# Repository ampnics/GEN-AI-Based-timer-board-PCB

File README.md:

Gen-AI-Based Timer Board using KiCad and DeepSeek
This project demonstrates the design of a timer control board created using traditional EDA tools supported by generative AI guidance. The goal was to explore how AI can assist in real-world hardware development, from concept to PCB.

Overview
This timer board is designed for applications such as:

Delay-based relay switching

Countdown-based automation

General purpose timing control in embedded systems

It features an ESP-based controller, a relay driver circuit, an OLED display for user feedback, and input buttons for setting time values.

AI Collaboration using DeepSeek
Throughout the project, DeepSeek AI was used to accelerate and refine different stages of the hardware design process:

Block Diagram: AI-generated block-level architecture based on system description.

Schematic Design: Assisted in part selection, logic validation, and drawing guidance.

Design Review: Suggested improvements for schematic correctness and layout optimization.

PCB Layout: Provided tips for routing, placement, EMI handling, and power distribution.

Design Feedback: Rated final design and recommended minor refinements.

Tools Used
KiCad 7.x for schematic and PCB design

DeepSeek AI for design assistance and review

ESP-based microcontroller

Relay module and driver circuitry

OLED I2C display

Tactile push buttons

Repository Structure
/kicad_project: Contains KiCad schematic and PCB layout files

/gerbers: Fabrication-ready Gerber files

/images: Block diagram, schematic snapshots, and board render

/docs: Design notes, AI feedback logs, and changelog

How to Use
Clone the repository

Open the KiCad project from the kicad_project folder

Review or modify the schematic as needed

Generate or inspect Gerber files for fabrication

Refer to the /docs folder for design rationale and review feedback

License
This project is open-sourced under the MIT License. You are free to use, modify, and distribute it for personal or commercial use.

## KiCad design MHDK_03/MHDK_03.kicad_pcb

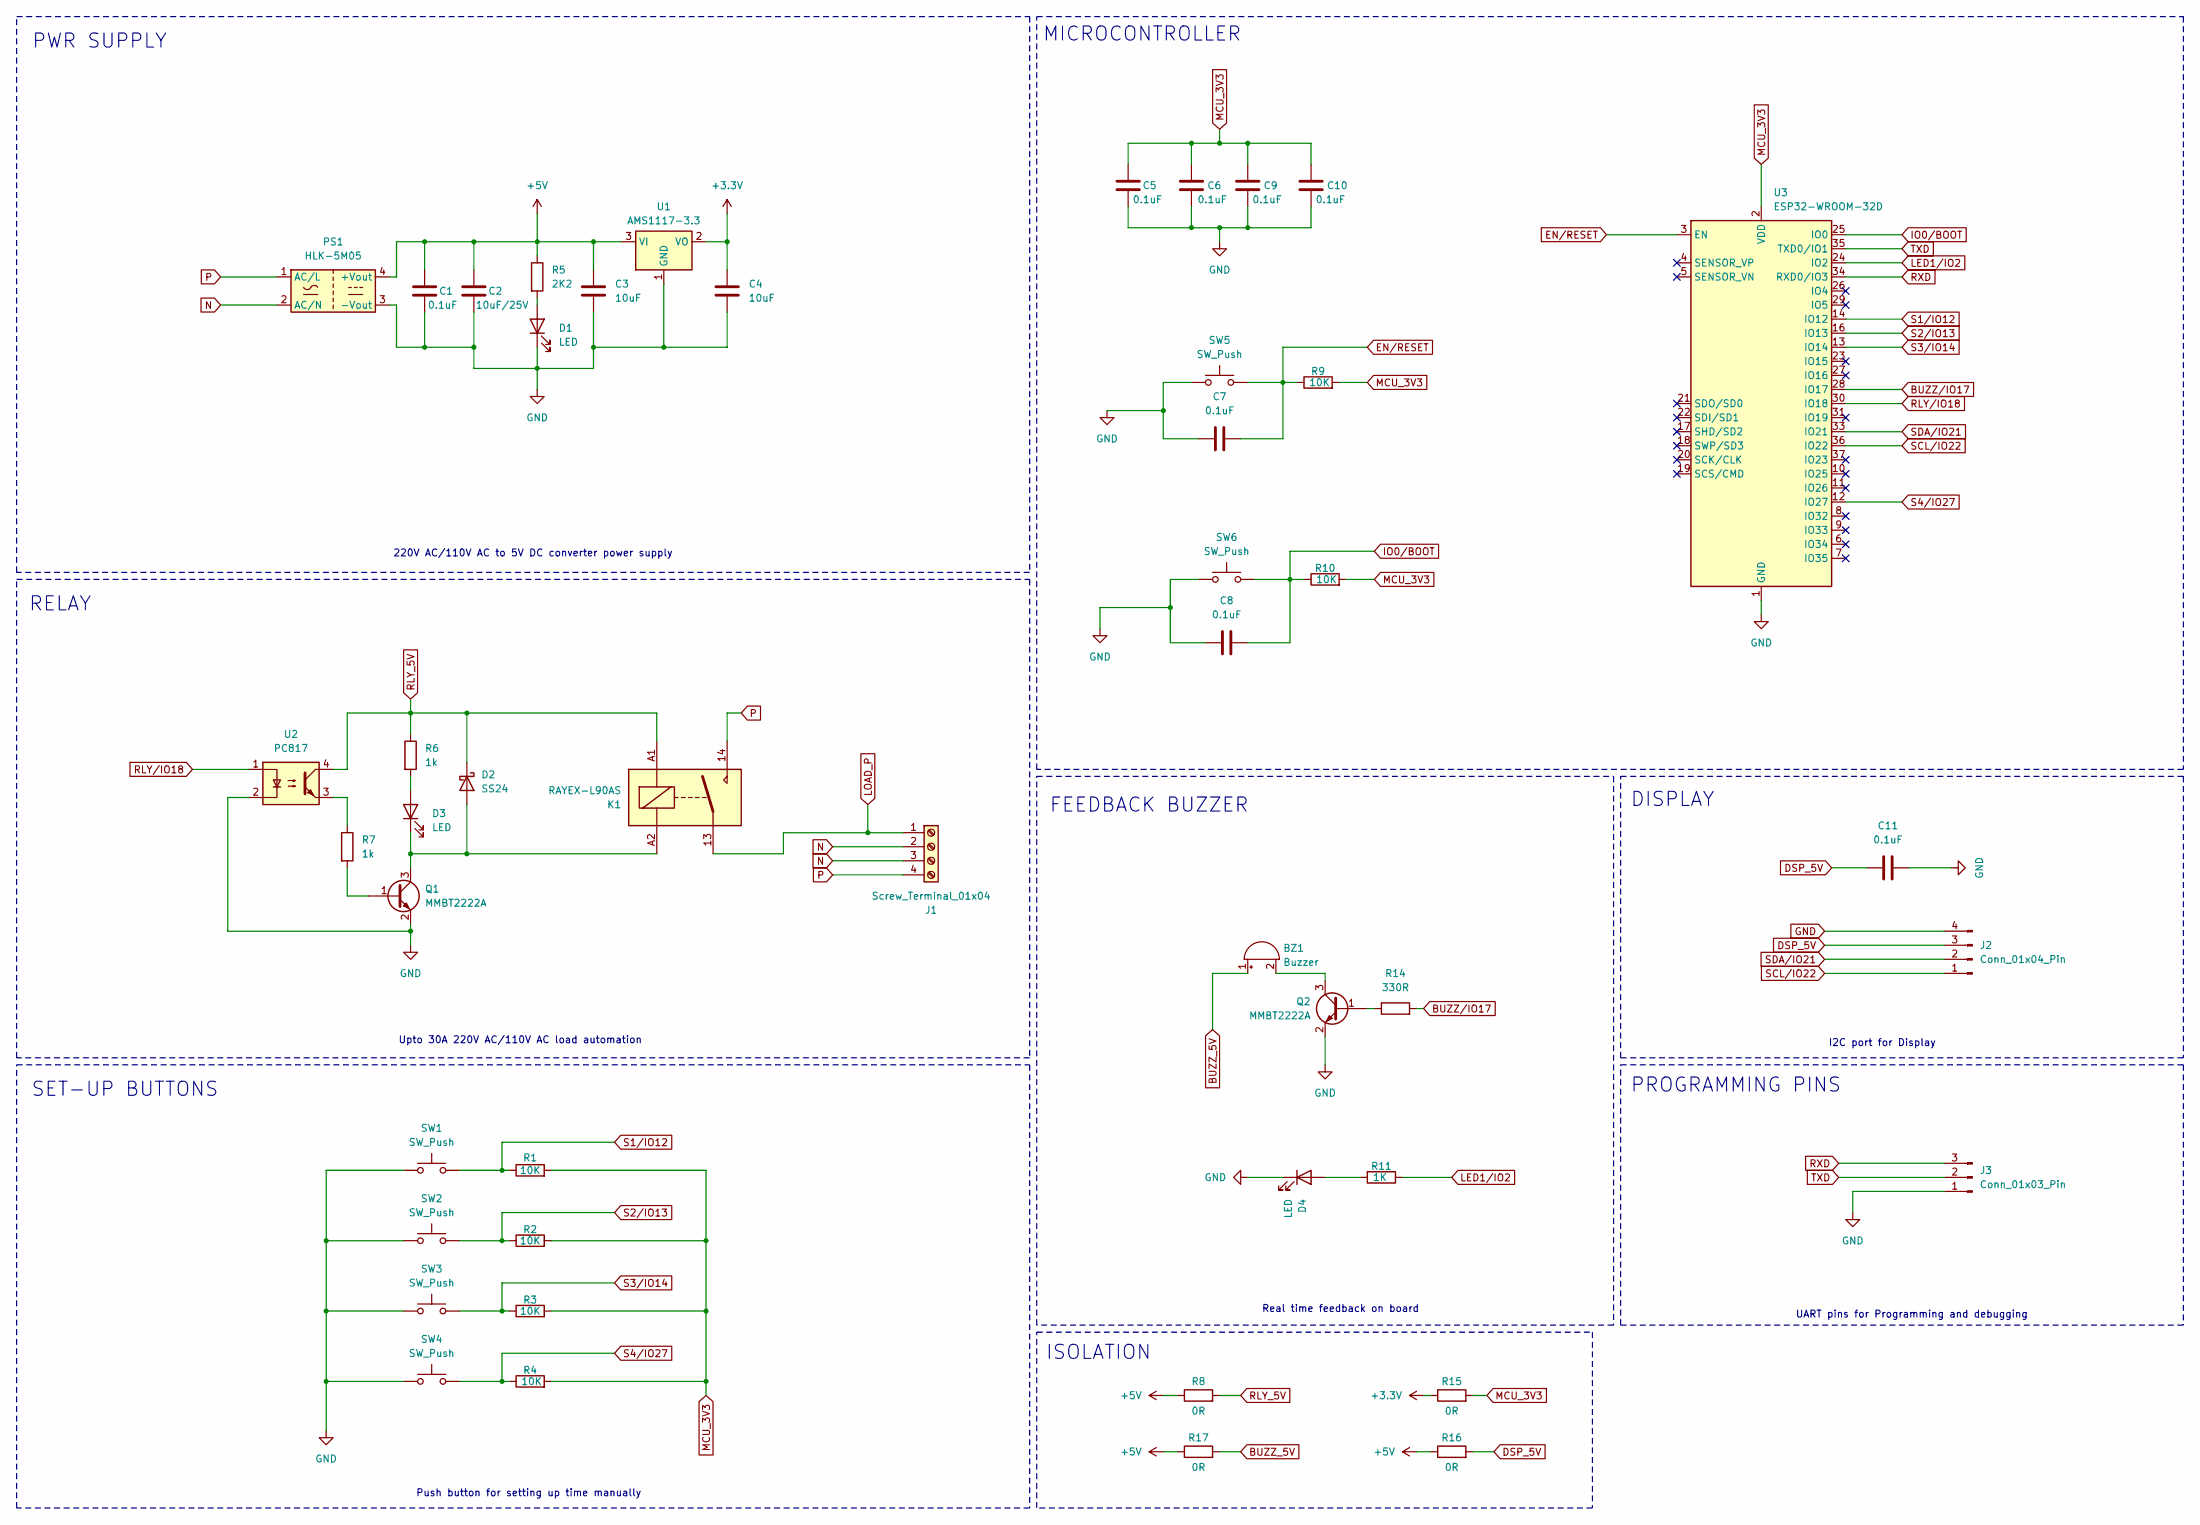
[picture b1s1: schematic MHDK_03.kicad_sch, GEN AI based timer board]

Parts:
BZ1: Buzzer; Buzzer_12x9.5RM7.6
C1, C5, C6, C7, C8, C9, C10, C11: 0.1uF; C_0805_2012Metric
C2: 10uF/25V; C_1206_3216Metric
C3, C4: 10uF; C_1206_3216Metric
D1, D3, D4: LED; LED_0805_2012Metric
D2: SS24; D_SMA
J1: Screw_Terminal_01x04; TerminalBlock_bornier-4_P5.08mm
J2: Conn_01x04_Pin; JST_XH_B4B-XH-A_1x04_P2.50mm_Vertical
J3: Conn_01x03_Pin; PinSocket_1x03_P2.54mm_Vertical
K1: RAYEX-L90AS; Relay_SPST_RAYEX-L90AS
PS1: HLK-5M05; Converter_ACDC_Hi-Link_HLK-5Mxx
Q1, Q2: MMBT2222A; SOT-23
R1, R2, R3, R4, R9, R10: 10K; R_0805_2012Metric
R5: 2K2; R_0805_2012Metric
R6, R7: 1k; R_0805_2012Metric
R8: 0R; R_0805_2012Metric
R11: 1K; R_0805_2012Metric
R14: 330R; R_0805_2012Metric
R15, R16, R17: 0R; R_0603_1608Metric
SW1, SW2, SW3, SW4, SW5: SW_Push; SW_PUSH_6mm
SW6: SW_Push; SW_Push_SPST_NO_Alps_SKRK
U1: AMS1117-3.3; SOT-223-3_TabPin2
U2: PC817; DIP-4_W7.62mm
U3: ESP32-WROOM-32D

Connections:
+3.3V: C4.1, R15.1, U1.2 (VO)
+5V: C1.1, C2.1, C3.1, PS1.4 (+Vout), R5.1, R8.1, R16.1, R17.1, U1.3 (VI)
BUZZ_5V: BZ1.1 (+), R17.2
BUZZ/IO17: R14.2, U3.28 (IO17)
DSP_5V: C11.2, J2.3, R16.2
EN/RESET: C7.2, R9.1, SW5.2, U3.3 (EN)
GND: C1.2, C2.2, C3.2, C4.2, C5.2, C6.2, C7.1, C8.1, C9.2, C10.2, C11.1, D1.1 (K), D4.1 (K), J2.4, J3.1, PS1.3 (-Vout), Q1.2 (E), Q2.2 (E), SW1.1, SW2.1, SW3.1, SW4.1, SW5.1, SW6.1, U1.1 (GND), U2.2, U3.1 (GND), U3.15 (GND), U3.38 (GND), U3.39 (GND)
IO0/BOOT: C8.2, R10.1, SW6.2, U3.25 (IO0)
LED1/IO2: R11.1, U3.24 (IO2)
LOAD_P: J1.1, K1.13
MCU_3V3: C5.1, C6.1, C9.1, C10.1, R1.2, R2.2, R3.2, R4.2, R9.2, R10.2, R15.2, U3.2 (VDD)
N: J1.2, J1.3, PS1.2 (AC/N)
unnamed: BZ1.2 (-), Q2.3 (C)
unnamed: D1.2 (A), R5.2
unnamed: D2.2 (A), D3.1 (K), K1.A2, Q1.3 (C)
unnamed: D3.2 (A), R6.2
unnamed: D4.2 (A), R11.2
unnamed: Q1.1 (B), R7.2
unnamed: Q2.1 (B), R14.1
unnamed: R7.1, U2.3
P: J1.4, K1.14, PS1.1 (AC/L)
RLY_5V: D2.1 (K), K1.A1, R6.1, R8.2, U2.4
RLY/IO18: U2.1, U3.30 (IO18)
RXD: J3.3, U3.34 (RXD0/IO3)
S1/IO12: R1.1, SW1.2, U3.14 (IO12)
S2/IO13: R2.1, SW2.2, U3.16 (IO13)
S3/IO14: R3.1, SW3.2, U3.13 (IO14)
S4/IO27: R4.1, SW4.2, U3.12 (IO27)
SCL/IO22: J2.1, U3.36 (IO22)
SDA/IO21: J2.2, U3.33 (IO21)
TXD: J3.2, U3.35 (TXD0/IO1)

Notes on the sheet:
Push button for setting up time manually
Real time feedback on board
RELAY
SET-UP BUTTONS
Upto 30A 220V AC/110V AC load automation
PROGRAMMING PINS
I2C port for Display
MICROCONTROLLER
PWR SUPPLY
ISOLATION
DISPLAY
220V AC/110V AC to 5V DC converter power supply
UART pins for Programming and debugging
FEEDBACK BUZZER

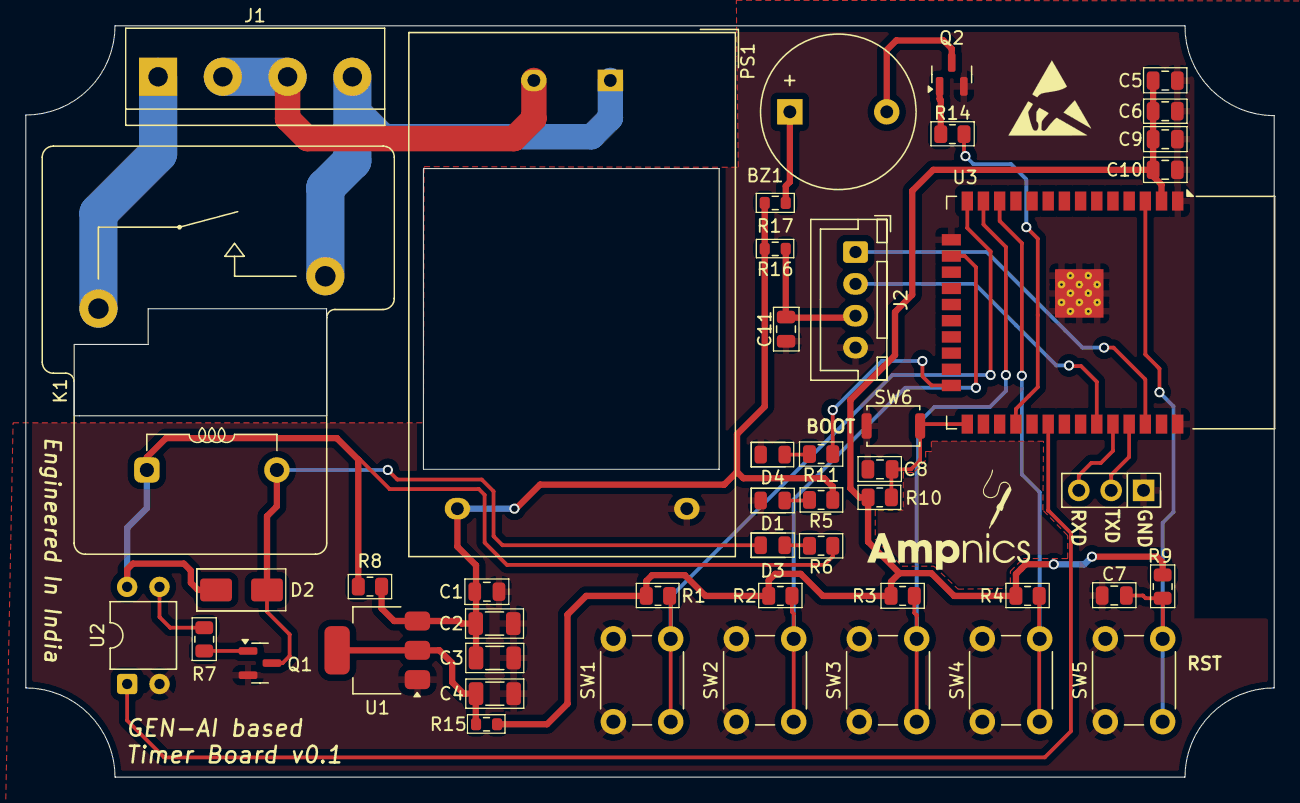
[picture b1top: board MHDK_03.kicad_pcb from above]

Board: 2 copper layers, 97.9 x 58.9 mm, 47 parts (0 on the bottom side), 31 nets.

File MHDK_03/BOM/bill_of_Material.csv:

"Reference","Qty","Value","DNP","Exclude from BOM","Exclude from Board","Footprint","Datasheet"
"BZ1","1","Buzzer","","","","Buzzer_Beeper:Buzzer_12x9.5RM7.6","~"
"C1,C5,C6,C7,C8,C9,C10,C11","8","0.1uF","","","","Capacitor_SMD:C_0805_2012Metric","~"
"C2","1","10uF/25V","","","","Capacitor_SMD:C_1206_3216Metric","~"
"C3,C4","2","10uF","","","","Capacitor_SMD:C_1206_3216Metric","~"
"D1,D3,D4","3","LED","","","","LED_SMD:LED_0805_2012Metric","~"
"D2","1","SS24","","","","Diode_SMD:D_SMA","https://www.vishay.com/docs/88748/ss22.pdf"
"J1","1","Screw_Terminal_01x04","","","","TerminalBlock:TerminalBlock_bornier-4_P5.08mm","~"
"J2","1","Conn_01x04_Pin","","","","Connector_JST:JST_XH_B4B-XH-A_1x04_P2.50mm_Vertical","~"
"J3","1","Conn_01x03_Pin","","","","Connector_PinSocket_2.54mm:PinSocket_1x03_P2.54mm_Vertical","~"
"K1","1","RAYEX-L90AS","","","","Relay_THT:Relay_SPST_RAYEX-L90AS","https://a3.sofastcdn.com/attachment/7jioKBjnRiiSrjrjknRiwS77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"
"PS1","1","HLK-5M05","","","","Converter_ACDC:Converter_ACDC_Hi-Link_HLK-5Mxx","http://h.hlktech.com/download/ACDC%E7%94%B5%E6%BA%90%E6%A8%A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"
"Q1,Q2","2","MMBT2222A","","","","Package_TO_SOT_SMD:SOT-23","https://assets.nexperia.com/documents/data-sheet/MMBT2222A.pdf"
"R1,R2,R3,R4,R9,R10","6","10K","","","","Resistor_SMD:R_0805_2012Metric","~"
"R5","1","2K2","","","","Resistor_SMD:R_0805_2012Metric","~"
"R6,R7","2","1k","","","","Resistor_SMD:R_0805_2012Metric","~"
"R8","1","0R","","","","Resistor_SMD:R_0805_2012Metric","~"
"R11","1","1K","","","","Resistor_SMD:R_0805_2012Metric","~"
"R14","1","330R","","","","Resistor_SMD:R_0805_2012Metric","~"
"R15,R16,R17","3","0R","","","","Resistor_SMD:R_0603_1608Metric","~"
"SW1,SW2,SW3,SW4,SW5","5","SW_Push","","","","Button_Switch_THT:SW_PUSH_6mm","~"
"SW6","1","SW_Push","","","","Button_Switch_SMD:SW_Push_SPST_NO_Alps_SKRK","~"
"U1","1","AMS1117-3.3","","","","Package_TO_SOT_SMD:SOT-223-3_TabPin2","http://www.advanced-monolithic.com/pdf/ds1117.pdf"
"U2","1","PC817","","","","Package_DIP:DIP-4_W7.62mm","http://www.soselectronic.cz/a_info/resource/d/pc817.pdf"
"U3","1","ESP32-WROOM-32D","","","","RF_Module:ESP32-WROOM-32D","https://www.espressif.com/sites/default/files/documentation/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"

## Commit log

2025-04-19 README.md
